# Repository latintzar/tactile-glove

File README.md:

# Artisan Glove

Artisan Glove is a precision glove for recording surface texture, contact and video.

[Website](https://atelierneyra.com/hardware/tactile-glove) · [Documentation](https://docs.atelierneyra.com/tactile-glove/overview/)

The glove lets people collect touch data while they work. The current exploration is a flexible, textured black nitrile glove targeting thousands of taxels across the hand, with recording electronics and a camera at the wrist.

## Dense tactile skin

The compact graphite cuff, hand-facing camera and forest-green pull tab carry through this new typology. Sensing-layer, readout and integration choices are the current investigation. The [dense sensing view](https://atelierneyra.com/hardware/tactile-glove#sensing) visualises 4,096 proposed taxel positions on the same hand photograph. [Current investigation](docs/dense-tactile-skin.md) records the target and engineering questions.

The source below records the earlier twenty-site V4 hardware and Bela experiments.

## Material signatures

In my piezo experiment, I saw distinct spectral signatures for aluminium, wood and sandpaper. Sandpaper had the largest bright feature in the middle of the frequency range; wood a small, thin ridge; aluminium a small-to-medium feature.

*Recreated from my observations.* [Reproduce the figure](docs/material-signatures/README.md).

## Earlier V4 hardware

Twenty sensing locations combine pressure-sensitive film and PVDF vibration sensors. Two IMUs distinguish wrist/camera motion from the hand; an ESP32-S3 records timestamped streams and camera frames to microSD, with USB, Wi-Fi and a browser monitor for inspection. It is a reusable engineering project for people building tactile capture hardware, signal-processing experiments and wearable acquisition systems.

## Source

[Explore CAD](https://atelierneyra.com/hardware/tactile-glove/viewer/) · [Product tour](docs/product-tour.md) · [Native PCB](hardware/glove-v4/electrical/glove-v4-routing-candidate.kicad_pcb) · [Enclosure parts](hardware/glove-v4/enclosure/)

[Setup](docs/setup.md) covers local inspection and the reusable firmware and hardware files.

## What you can explore

| Area | What you can do |
|---|---|
| Cuff design | Inspect the enclosure geometry, camera, battery, connectors, component envelopes and individual parts. |
| Sensing glove | Follow the twenty pressure/PVDF locations, material stack, cut patterns and keyed harness. |
| Electronics | Edit the native KiCad main board and schematics, dorsal IMU tile, footprints, component lists and net mappings. |
| Firmware | Inspect acquisition timing, bus ownership, power transitions, camera deadlines, storage, packet formats and the device browser UI. |
| Verification | Execute the production C++ core and HTTP logic on your computer, decode their actual output, and audit STL clearances. |
| Earlier experiments | Read the Bela sensing pilot and the earlier camera-free V3 board, with their achieved results and open questions kept explicit. |

## Earlier V4 stage

The recorded V4 source is an **engineering beta**. The ESP32-S3 target image was compiled; fresh host checks execute 34 core cases, 13 HTTP cases, 32 protocol/piezo cases and 9 camera-driver cases. The current 561-component V4 board has **20 unconnected items and zero saved physical DRC errors**. Its dorsal IMU tile includes fabrication outputs; the main board awaits routing and manufacturing qualification.

An assembled V4 glove, simultaneous acquisition/camera/radio timing, force calibration, enclosure acceptance and six-hour endurance remain physical validation steps. Rates below describe implementation settings and design targets. [Status and evidence](docs/status.md) distinguish each stage.

The current thin-glove appearance and surgery/sport scenes illustrate the dense tactile-skin investigation. [Design history](docs/design-history.md) records the earlier native V4 geometry and actual validation stage.

| Stream | Implementation setting |
|---|---|
| Pressure | 20 locations × 50 samples/s; electrical levels until per-cell force calibration |
| PVDF vibration | 20 locations × 4,000 samples/s |
| Motion | Two ISM330DHCX IMUs at 833 Hz |
| Camera | OV5640 VGA JPEG, approximately 10 fps target |
| Recording | Timestamped, checksummed tactile/motion streams and JPEG frames on microSD |
| Connections | USB and Wi-Fi full streams; BLE setup, status and selected data |

## Get started

Python 3.11 or later is enough to open the static design viewer:

```sh
git clone https://github.com/latintzar/tactile-glove.git
cd tactile-glove
python3 tools/serve.py
```

Open **http://127.0.0.1:8070/**. The viewer loads the supplied engineering geometry locally. [Setup](docs/setup.md) covers host tests, native KiCad editing, enclosure checks and the pinned ESP-IDF firmware build. Device assembly and programming have their own acceptance guide.

## Source and guides

- [Dense tactile-skin investigation](docs/dense-tactile-skin.md)
- [Product tour and complete journey](docs/product-tour.md)
- [Module map](docs/module-map.md) · [Architecture](docs/architecture.md)
- [Setup](docs/setup.md) · [Verification](docs/verification.md)
- [Current status](docs/status.md) · [Design history and decisions](docs/design-history.md)
- [V4 hardware guide](hardware/glove-v4/README.md) · [Firmware and protocol](firmware/tactile_v4/README.md)
- [Earlier Bela experiment](docs/bela-experiment.md)
- [Contributing and refreshing the inventory](CONTRIBUTING.md)
- [Source inventory and redistribution scope](docs/source-inventory.md) · [Third-party notices](THIRD-PARTY-NOTICES.md)

## Licence and credits

Peter Neyra’s original code, documentation and hardware design are [MIT licensed](LICENSE). Redistributed KiCad library files retain **CC BY-SA 4.0** with KiCad’s design-output exception; Espressif camera sources retain **Apache 2.0**; Seeed and viewer assets retain their own MIT notices. [Third-party notices](THIRD-PARTY-NOTICES.md) identify those boundaries and source revisions.

Made by [Atelier Neyra](https://atelierneyra.com/).

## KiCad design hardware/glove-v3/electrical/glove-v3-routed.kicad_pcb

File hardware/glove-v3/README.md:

# Right-hand tactile glove —V3.3 core

Current completed electrical baseline:20 separately read pressure locations and20 PVDF vibration locations, one button and a diffused RGB indicator. The next complete-product requirement adds continuous finger-facing video for at least six hours, with twelve hours as the stretch target. Its camera, controller and larger-battery power design remain under integration review.

## Files

- `electrical/components.json`:356 fitted components,244 nets,1125 connected endpoints and19 intentional NC pins;40 MPN groups.
- `electrical/glove-v3.kicad_sch`: native schematic; `electrical/glove-v3-routed.kicad_pcb`:90×60×1.6mm four-layer routing. Native reconciliation and KiCad DRC report zero violations, opens or footprint errors.
- `electrical/manufacturing/manifest.json`:18 hashed manufacturing files, Gerbers/drills,356-placement CPL and actual-board assembly drawings. VIPPO epoxy-filled, planarized, copper-capped vias are mandatory at34 SMD-overlap locations.
- `../../firmware/tactile_v3/`: compiled XIAO nRF52840 firmware,130688 bytes flash/21408 bytes static RAM; matching HEX/UF2/debug ELF and source hashes.
- `../../tools/tactile_v3/`: transport, recording and Bluetooth bridge. Wireprotocol2 explicitly records3V reference,1.25V midpoint and2.5V excitation.
- `guide/index.html`, `sensors/assembly.md`, `sensors/wiring.csv`:20 anatomical locations, film orientation, stack construction and six keyed harness branches.
- `enclosure/index.html`: existing500mAh core enclosure. `enclosure/pebble-concept/index.html`: separate rounded CAD concept with actual geometry and constraints; its106×82×34.56mm envelope is not a watch-size product. Camera/largerbattery integration is pending.
- `camera/runtime-and-integration.md`, `camera/runtime-budget.json`, `camera/camera-selection.md`: six-hour power ceiling, exact battery candidate, optics and heat checks, with sources.
- `procurement/jlc-v33/`: current quote files and exact-part availability/substitution records. The earlier V3.1/V3.2 quote artifacts are historical partial quotes.

## Verified in software and simulation

- `verification/final-software-v33.json`:488 distinct repository tests plus four subtests pass; JavaScript syntax passes.
- `verification/firmware-simulation.md`:41 actual-sketch scenarios pass ASan/UBSan, including acquisition, timing rollover, button, power qualification, malformed commands, transport faults, backpressure and IMU failures.
- `verification/signal-chain/piezo-end-to-end.md`:520 modeled ADC samples survive USB and BLE selected-channel transport exactly, with timestamps and six RMS/peak windows independently checked.
- `verification/power-simulation.md`: corrected reference, excitation buffer, shutdown/protection and component-current checks.
- `verification/analog-signal-chain.md`:16/18 primary Microchip/Nexperia transient cases complete; two late-recovery solver failures also complete with explicitly bounded1fF numerical stabilization. Seven TI mux/driver cases complete, informing6µs dynamic and12µs pressure waits.

These checks do not substitute for physical timing, radio, current, thermal or tactile characterization.

## Use of the tactile core

Hold the button0.8s from sleep and release to wake; continue to3s for a120s pairing window. While running, tap to pause/resume or hold1.5s to sleep after release. Blue indicates startup/pairing; green indicates ready/collecting; amber indicates low or unqualified battery; a red double flash indicates ADC trouble.

Target acquisition is20 vibration channels at4kS/s each and20 pressure channels at50S/s each. USB carries full raw data. BLE carries all-channel features or one selected raw channel plus IMU/health. Invalid-power and dropped-frame flags remain in recordings. The current battery configuration is a protected500mAh cell with100mA charging; it is not the six-hour camera system.

## Manufacturing and capability scope

The tactile board is a routed engineering prototype. Its specified VIPPO process, complete sourcing, assembly quote and first-article acceptance remain required. The camera integration changes the MCU/power/firmware design and enclosure; it is not yet a factory release. The initialUS$150–200 complete delivered target remains unverified. No purchase or email has been sent.

Pressure readings require cell calibration; vibration plots are signal measurements, not measured surface Ra. The hardware does not directly measure every finger joint or drift-free hidden-hand position. Rendering and demos must preserve those distinctions.

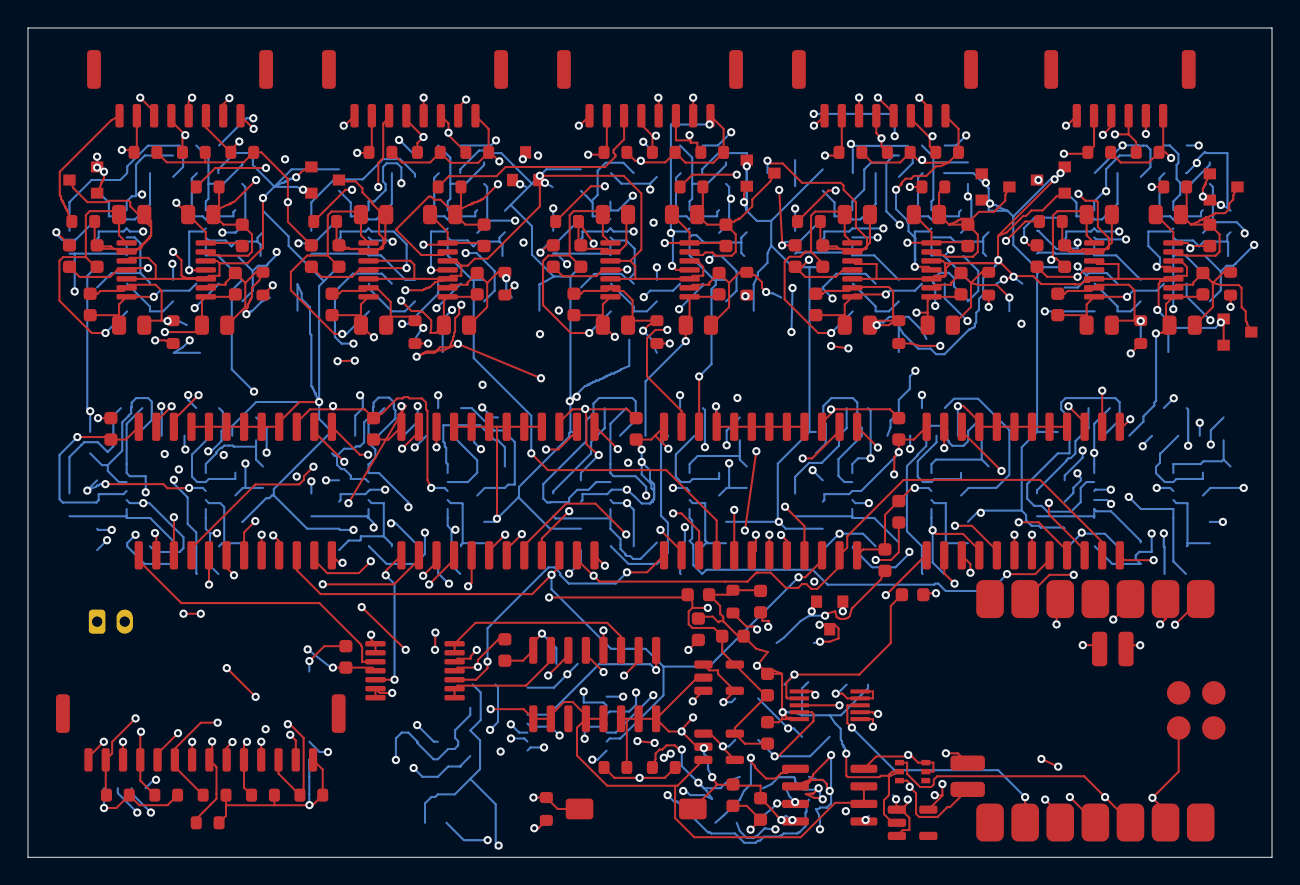
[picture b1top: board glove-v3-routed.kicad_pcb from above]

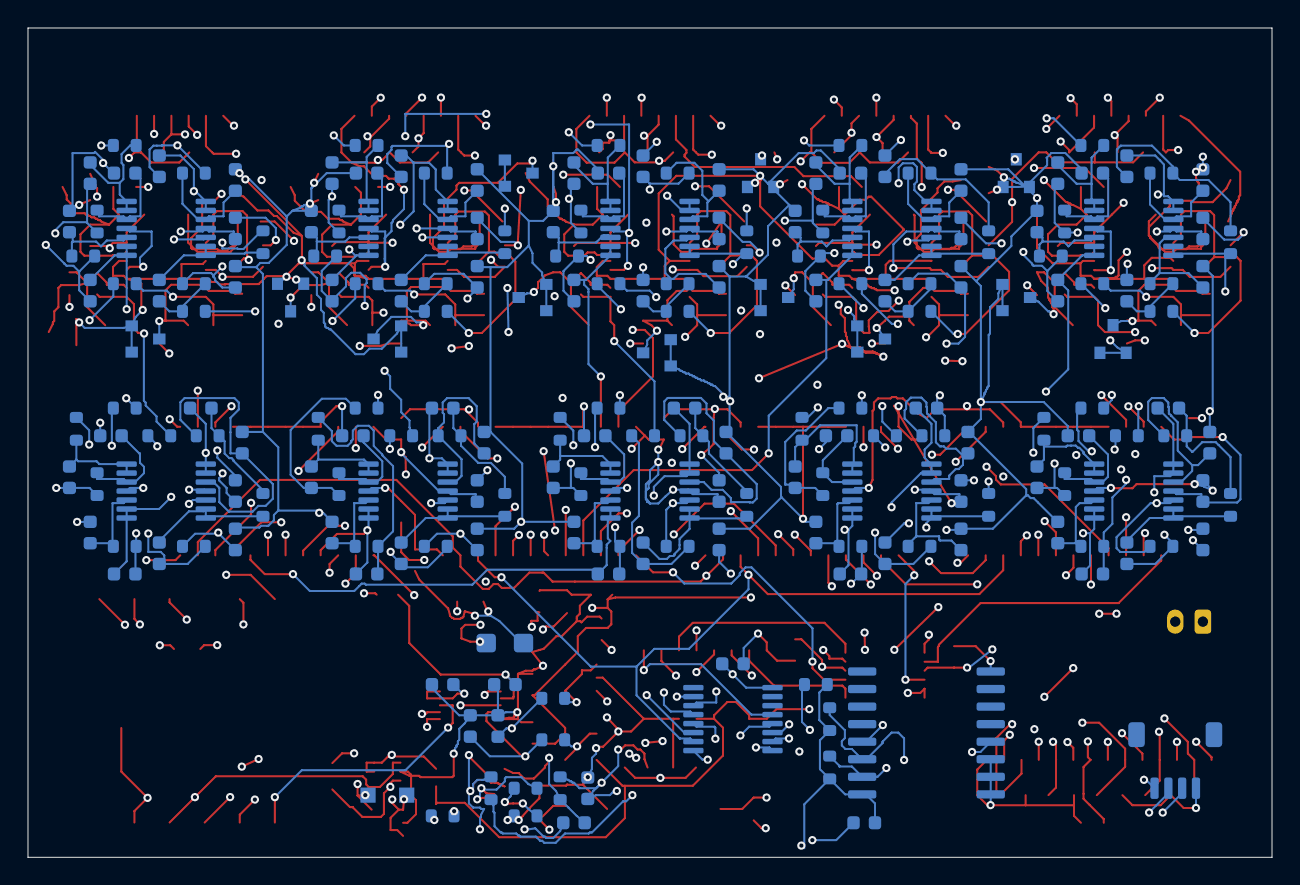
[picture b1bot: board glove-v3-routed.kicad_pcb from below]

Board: 4 copper layers, 90.0 x 60.0 mm, 356 parts (215 on the bottom side), 243 nets.

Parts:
C1, C6, C11, C16, C21, C26, C31, C36, C41, C46, C51, C56, C61, C66, C71, C76, C81, C86, C91, C96: GRM1885C1H471JA01D; C_0603_1608Metric
C2, C7, C12, C17, C22, C27, C32, C37, C42, C47, C52, C57, C62, C67, C72, C77, C82, C87, C92, C97: C0603C123J3GACAUTO; C_0603_1608Metric
C3, C8, C13, C18, C23, C28, C33, C38, C43, C48, C53, C58, C63, C68, C73, C78, C83, C88, C93, C98: GRM1885C1H103JA01D; C_0603_1608Metric
C4, C9, C14, C19, C24, C29, C34, C39, C44, C49, C54, C59, C64, C69, C74, C79, C84, C89, C94, C99: C0603C153J3GACAUTO; C_0603_1608Metric
C5, C10, C15, C20, C25, C30, C35, C40, C45, C50, C55, C60, C65, C70, C75, C80, C85, C90, C95, C100: GRM1885C1H222JA01D; C_0603_1608Metric
C101, C102, C103, C104, C108, C133, C135, C136, C141: GRM188R61A105KA61D; C_0603_1608Metric
C105, C107, C109, C110, C111, C112, C113, C114, C115, C116, C117, C118, C119, C120, C121, C122, C123, C124, C125, C126, C127, C128, C129, C130, C131, C132, C137, C140: GRM188R71H104KA93D; C_0603_1608Metric
C106: TAJA685K010RNJ; CP_EIA-3216-18_Kemet-A
C134, C138: GRM1885C1H102JA01D; C_0603_1608Metric
C139: GRM188R71C104KA01D; C_0603_1608Metric
D1: PMEG2010ER,115; D_SOD-123F
D2, D3, D4, D5, D6, D7, D8, D9, D10, D11, D12, D13, D14, D15, D16, D17, D18, D19, D20, D21: BAV199,215; SOT-23
J1: 102010469; XIAO-nRF52840-SMD-kicad7
J2: B2B-PH-K-S(LF)(SN); JST_PH_B2B-PH-K_1x02_P2.00mm_Vertical
J3: SM04B-SRSS-TB(LF)(SN); JST_SH_SM04B-SRSS-TB_1x04-1MP_P1.00mm_Horizontal
J5: BM06B-GHS-TBT(LF)(SN); JST_GH_BM06B-GHS-TBT_1x06-1MP_P1.25mm_Vertical
J6, J7, J8, J9: BM08B-GHS-TBT(LF)(SN); JST_GH_BM08B-GHS-TBT_1x08-1MP_P1.25mm_Vertical
J10: BM14B-GHS-TBT(LF)(SN); JST_GH_BM14B-GHS-TBT_1x14-1MP_P1.25mm_Vertical
R1, R8, R15, R22, R29, R36, R43, R50, R57, R64, R71, R78, R85, R92, R99, R106, R113, R120, R127, R134: RV0805FR-0722ML; R_0805_2012Metric
R2, R9, R16, R23, R30, R37, R44, R51, R58, R65, R72, R79, R86, R93, R100, R107, R114, R121, R128, R135, R146: RC0603FR-07100KL; R_0603_1608Metric
R3, R4, R10, R11, R17, R18, R24, R25, R31, R32, R38, R39, R45, R46, R52, R53, R59, R60, R66, R67, R73, R74, R80, R81, R87, R88, R94, R95, R101, R102, R108, R109, R115, R116, R122, R123, R129, R130, R136, R137: RC0603FR-0714K7L; R_0603_1608Metric
R5, R6, R12, R13, R19, R20, R26, R27, R33, R34, R40, R41, R47, R48, R54, R55, R61, R62, R68, R69, R75, R76, R82, R83, R89, R90, R96, R97, R103, R104, R110, R111, R117, R118, R124, R125, R131, R132, R138, R139: RC0603FR-0727K4L; R_0603_1608Metric
R7, R14, R21, R28, R35, R42, R49, R56, R63, R70, R77, R84, R91, R98, R105, R112, R119, R126, R133, R140, R141, R142, R147, R149, R151, R154: RC0603FR-0710KL; R_0603_1608Metric
R143, R148: RC0603FR-0722RL; R_0603_1608Metric
R144, R145, R152: RC0603FR-074K7L; R_0603_1608Metric
R150: RC0603FR-072KL; R_0603_1608Metric
R153: RC0603FR-0747RL; R_0603_1608Metric
SW1: PTS636SK43SMTR-LFS; SW_PTS636_SK43_G
U1: TLV75518PDBVR; SOT-23-5
U2: REF3330AIDBZR; SOT-23
U3: MCP6002T-I/SN; SOIC-8_3.9x4.9mm_P1.27mm
U4: MCP33131D-10-I/MS; MSOP-10_3x3mm_P0.5mm
U5, U29: OPA320AIDBVR; SOT-23-5
U6, U7, U8, U9: CD74HC4067M; SOIC-24W_7.5x15.4mm_P1.27mm
U10: CD74HC4052M; SOIC-16_3.9x9.9mm_P1.27mm
U11, U12, U13, U14, U15, U16, U17, U18, U19, U20, U21, U22, U23, U24, U25: MCP6004T-I/ST; TSSOP-14_4.4x5mm_P0.65mm
U26: OPA4323IPWR; TSSOP-14_4.4x5mm_P0.65mm
U27: TCA9534DWR; SOIC-16W_7.5x10.3mm_P1.27mm
U28: TPS22919DCKT; SOT-363_SC-70-6
U30: SN74AHC595PWR; TSSOP-16_4.4x5mm_P0.65mm

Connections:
1V8: C102.1, C104.1, D1.2, U1.5, U4.2
3V3: C132.1, C135.1, J1.12, J3.2, R144.1, R145.1, R147.1, R149.1, U27.16, U28.1
3V3A: C101.1, C105.1, C107.1, C108.1, C109.1, C110.1, C111.1, C112.1, C113.1, C114.1, C115.1, C116.1, C117.1, C118.1, C119.1, C120.1, C121.1, C122.1, C123.1, C124.1, C125.1, C126.1, C127.1, C128.1, C129.1, C130.1, C131.1, C136.1, C137.1, C139.1, D1.1, U1.1, U1.3, U2.1, U3.8, U4.9, U4.10, U5.5, U6.24, U7.24, U8.24, U9.24, U10.16, U11.4, U12.4, U13.4, U14.4, U15.4, U16.4, U17.4, U18.4, U19.4, U20.4, U21.4, U22.4, U23.4, U24.4, U25.4, U26.4, U28.5, U28.6, U29.5, U30.10, U30.16
ADC_AIN+: C134.1, R143.2, U4.3
ADC_AIN-: C138.1, R148.2, U4.4
ADC_CNV: J1.11, U4.6
ADC_DRIVER_OUT: R143.1, U5.1, U5.4
ADC_MISO: J1.10, U4.7
ADC_MUX: U5.3, U10.13
ADC_NEG_OUT: R148.1, U29.1, U29.4
ADC_SCK: J1.9, U4.8
ANALOG_EN: J1.22, R146.1, U28.3
BAT+: J1.19, J2.1
BTN0: R149.2, SW1.1, U27.4
CHG_IN_H1: C91.2, D20.3, R127.2, R128.2, U15.9
CHG_IN_H2: C96.2, D21.3, R134.2, R135.2, U15.13
CHG_IN_I1: C1.2, D2.3, R1.2, R2.2, U11.2
CHG_IN_I2: C6.2, D3.3, R8.2, R9.2, U11.6
CHG_IN_I3: C11.2, D4.3, R15.2, R16.2, U11.9
CHG_IN_L1: C46.2, D11.3, R64.2, R65.2, U13.6
CHG_IN_L2: C51.2, D12.3, R71.2, R72.2, U13.9
CHG_IN_L3: C56.2, D13.3, R78.2, R79.2, U13.13
CHG_IN_M1: C16.2, D5.3, R22.2, R23.2, U11.13
CHG_IN_M2: C21.2, D6.3, R29.2, R30.2, U12.2
CHG_IN_M3: C26.2, D7.3, R36.2, R37.2, U12.6
CHG_IN_P1: C71.2, D16.3, R99.2, R100.2, U14.9
CHG_IN_P2: C76.2, D17.3, R106.2, R107.2, U14.13
CHG_IN_P3: C81.2, D18.3, R113.2, R114.2, U15.2
CHG_IN_P4: C86.2, D19.3, R120.2, R121.2, U15.6
CHG_IN_R1: C31.2, D8.3, R43.2, R44.2, U12.9
CHG_IN_R2: C36.2, D9.3, R50.2, R51.2, U12.13
CHG_IN_R3: C41.2, D10.3, R57.2, R58.2, U13.2
CHG_IN_T1: C61.2, D14.3, R85.2, R86.2, U14.2
CHG_IN_T2: C66.2, D15.3, R92.2, R93.2, U14.6
CHG_OUT_H1: C91.1, R127.1, R129.1, U15.8
CHG_OUT_H2: C96.1, R134.1, R136.1, U15.14
CHG_OUT_I1: C1.1, R1.1, R3.1, U11.1
CHG_OUT_I2: C6.1, R8.1, R10.1, U11.7
CHG_OUT_I3: C11.1, R15.1, R17.1, U11.8
CHG_OUT_L1: C46.1, R64.1, R66.1, U13.7
CHG_OUT_L2: C51.1, R71.1, R73.1, U13.8
CHG_OUT_L3: C56.1, R78.1, R80.1, U13.14
CHG_OUT_M1: C16.1, R22.1, R24.1, U11.14
CHG_OUT_M2: C21.1, R29.1, R31.1, U12.1
CHG_OUT_M3: C26.1, R36.1, R38.1, U12.7
CHG_OUT_P1: C71.1, R99.1, R101.1, U14.8
CHG_OUT_P2: C76.1, R106.1, R108.1, U14.14
CHG_OUT_P3: C81.1, R113.1, R115.1, U15.1
CHG_OUT_P4: C86.1, R120.1, R122.1, U15.7
CHG_OUT_R1: C31.1, R43.1, R45.1, U12.8
CHG_OUT_R2: C36.1, R50.1, R52.1, U12.14
CHG_OUT_R3: C41.1, R57.1, R59.1, U13.1
CHG_OUT_T1: C61.1, R85.1, R87.1, U14.1
CHG_OUT_T2: C66.1, R92.1, R94.1, U14.7
GND: C101.2, C102.2, C103.2, C104.2, C105.2, C106.2, C107.2, C108.2, C109.2, C110.2, C111.2, C112.2, C113.2, C114.2, C115.2, C116.2, C117.2, C118.2, C119.2, C120.2, C121.2, C122.2, C123.2, C124.2, C125.2, C126.2, C127.2, C128.2, C129.2, C130.2, C131.2, C132.2, C133.2, C134.2, C135.2, C136.2, C137.2, C138.2, C139.2, C141.2, J1.13, J1.18, J1.20, J2.2, J3.1, J5.6, J6.8, J7.8, J8.8, J9.8, J10.14, R7.2, R14.2, R21.2, R28.2, R35.2, R42.2, R49.2, R56.2, R63.2, R70.2, R77.2, R84.2, R91.2, R98.2, R105.2, R112.2, R119.2, R126.2, R133.2, R140.2, R142.2, R146.2, R151.2, SW1.2, U1.2, U2.3, U3.4, U4.5, U5.2, U6.12, U6.15, U7.12, U7.15, U8.12, U8.15, U9.12, U9.15, U10.6, U10.7, U10.8, U11.11, U12.11, U13.11, U14.11, U15.11, U16.11, U17.11, U18.11, U19.11, U20.11, U21.11, U22.11, U23.11, U24.11, U25.11, U26.11, U27.1, U27.2, U27.3, U27.8, U28.2, U29.2, U30.8, U30.13
I2C_SCL: J1.6, J3.4, R145.2, U27.14
I2C_SDA: J1.5, J3.3, R144.2, U27.15
MUX1_BUF: U10.12, U26.1, U26.2
MUX1_COM: U6.1, U26.3
MUX2_BUF: U10.14, U26.6, U26.7
MUX2_COM: U7.1, U26.5
MUX3_BUF: U10.15, U26.8, U26.9
MUX3_COM: U8.1, U26.10
MUX4_BUF: U10.11, U26.13, U26.14
MUX4_COM: U9.1, U26.12
MUX_A0: U6.10, U7.10, U8.10, U9.10, U30.15
MUX_A1: U6.11, U7.11, U8.11, U9.11, U30.1
MUX_A2: U6.14, U7.14, U8.14, U9.14, U30.2
MUX_A3: U6.13, U7.13, U8.13, U9.13, U30.3
MUX_BANK0: U10.10, U30.4
MUX_BANK1: U10.9, U30.5
MUX_RCLK: J1.3, U30.12
MUX_SER: J1.2, U30.14
MUX_SRCLK: J1.1, U30.11
PRESS_H1: J10.10, R133.1, U7.23
PRESS_H2: J10.12, R140.1, U7.22
PRESS_I1: J6.2, R7.1, U6.9
PRESS_I2: J6.4, R14.1, U6.8
PRESS_I3: J6.6, R21.1, U6.7
PRESS_L1: J9.2, R70.1, U6.22
PRESS_L2: J9.4, R77.1, U7.9
PRESS_L3: J9.6, R84.1, U7.8
PRESS_M1: J7.2, R28.1, U6.6
PRESS_M2: J7.4, R35.1, U6.5
PRESS_M3: J7.6, R42.1, U6.4
PRESS_P1: J10.2, R105.1, U7.5
PRESS_P2: J10.4, R112.1, U7.4
PRESS_P3: J10.6, R119.1, U7.3
PRESS_P4: J10.8, R126.1, U7.2
PRESS_R1: J8.2, R49.1, U6.3
PRESS_R2: J8.4, R56.1, U6.2
PRESS_R3: J8.6, R63.1, U6.23
PRESS_T1: J5.2, R91.1, U7.7
PRESS_T2: J5.4, R98.1, U7.6
PVDF_H1: J10.9, R128.1
PVDF_H2: J10.11, R135.1
PVDF_I1: J6.1, R2.1
PVDF_I2: J6.3, R9.1
PVDF_I3: J6.5, R16.1
PVDF_L1: J9.1, R65.1
PVDF_L2: J9.3, R72.1
PVDF_L3: J9.5, R79.1
PVDF_M1: J7.1, R23.1
PVDF_M2: J7.3, R30.1
PVDF_M3: J7.5, R37.1
PVDF_P1: J10.1, R100.1
PVDF_P2: J10.3, R107.1
PVDF_P3: J10.5, R114.1
PVDF_P4: J10.7, R121.1
PVDF_R1: J8.1, R44.1
PVDF_R2: J8.3, R51.1
PVDF_R3: J8.5, R58.1
PVDF_T1: J5.1, R86.1
PVDF_T2: J5.3, R93.1
S1_A_H1: C92.1, R129.2, R130.1
S1_A_H2: C97.1, R136.2, R137.1
S1_A_I1: C2.1, R3.2, R4.1
S1_A_I2: C7.1, R10.2, R11.1
S1_A_I3: C12.1, R17.2, R18.1
S1_A_L1: C47.1, R66.2, R67.1
S1_A_L2: C52.1, R73.2, R74.1
S1_A_L3: C57.1, R80.2, R81.1
S1_A_M1: C17.1, R24.2, R25.1
S1_A_M2: C22.1, R31.2, R32.1
S1_A_M3: C27.1, R38.2, R39.1
S1_A_P1: C72.1, R101.2, R102.1
S1_A_P2: C77.1, R108.2, R109.1
S1_A_P3: C82.1, R115.2, R116.1
S1_A_P4: C87.1, R122.2, R123.1
S1_A_R1: C32.1, R45.2, R46.1
S1_A_R2: C37.1, R52.2, R53.1
S1_A_R3: C42.1, R59.2, R60.1
S1_A_T1: C62.1, R87.2, R88.1
S1_A_T2: C67.1, R94.2, R95.1
S1_B_H1: C93.1, R130.2, U25.3
S1_B_H2: C98.1, R137.2, U25.10
S1_B_I1: C3.1, R4.2, U16.3
S1_B_I2: C8.1, R11.2, U16.10
S1_B_I3: C13.1, R18.2, U17.3
S1_B_L1: C48.1, R67.2, U20.10
S1_B_L2: C53.1, R74.2, U21.3
S1_B_L3: C58.1, R81.2, U21.10
S1_B_M1: C18.1, R25.2, U17.10
S1_B_M2: C23.1, R32.2, U18.3
S1_B_M3: C28.1, R39.2, U18.10
S1_B_P1: C73.1, R102.2, U23.3
S1_B_P2: C78.1, R109.2, U23.10
S1_B_P3: C83.1, R116.2, U24.3
S1_B_P4: C88.1, R123.2, U24.10
S1_B_R1: C33.1, R46.2, U19.3
S1_B_R2: C38.1, R53.2, U19.10
S1_B_R3: C43.1, R60.2, U20.3
S1_B_T1: C63.1, R88.2, U22.3
S1_B_T2: C68.1, R95.2, U22.10
S1_OUT_H1: C92.2, R131.1, U25.1, U25.2
S1_OUT_H2: C97.2, R138.1, U25.8, U25.9
S1_OUT_I1: C2.2, R5.1, U16.1, U16.2
S1_OUT_I2: C7.2, R12.1, U16.8, U16.9
S1_OUT_I3: C12.2, R19.1, U17.1, U17.2
S1_OUT_L1: C47.2, R68.1, U20.8, U20.9
S1_OUT_L2: C52.2, R75.1, U21.1, U21.2
S1_OUT_L3: C57.2, R82.1, U21.8, U21.9
S1_OUT_M1: C17.2, R26.1, U17.8, U17.9
S1_OUT_M2: C22.2, R33.1, U18.1, U18.2
S1_OUT_M3: C27.2, R40.1, U18.8, U18.9
S1_OUT_P1: C72.2, R103.1, U23.1, U23.2
S1_OUT_P2: C77.2, R110.1, U23.8, U23.9
S1_OUT_P3: C82.2, R117.1, U24.1, U24.2
S1_OUT_P4: C87.2, R124.1, U24.8, U24.9
S1_OUT_R1: C32.2, R47.1, U19.1, U19.2
S1_OUT_R2: C37.2, R54.1, U19.8, U19.9
S1_OUT_R3: C42.2, R61.1, U20.1, U20.2
S1_OUT_T1: C62.2, R89.1, U22.1, U22.2
S1_OUT_T2: C67.2, R96.1, U22.8, U22.9
S2_A_H1: C94.1, R131.2, R132.1
S2_A_H2: C99.1, R138.2, R139.1
S2_A_I1: C4.1, R5.2, R6.1
S2_A_I2: C9.1, R12.2, R13.1
S2_A_I3: C14.1, R19.2, R20.1
S2_A_L1: C49.1, R68.2, R69.1
S2_A_L2: C54.1, R75.2, R76.1
S2_A_L3: C59.1, R82.2, R83.1
S2_A_M1: C19.1, R26.2, R27.1
S2_A_M2: C24.1, R33.2, R34.1
S2_A_M3: C29.1, R40.2, R41.1
S2_A_P1: C74.1, R103.2, R104.1
S2_A_P2: C79.1, R110.2, R111.1
S2_A_P3: C84.1, R117.2, R118.1
S2_A_P4: C89.1, R124.2, R125.1
S2_A_R1: C34.1, R47.2, R48.1
S2_A_R2: C39.1, R54.2, R55.1
S2_A_R3: C44.1, R61.2, R62.1
S2_A_T1: C64.1, R89.2, R90.1
S2_A_T2: C69.1, R96.2, R97.1
S2_B_H1: C95.1, R132.2, U25.5
S2_B_H2: C100.1, R139.2, U25.12
S2_B_I1: C5.1, R6.2, U16.5
S2_B_I2: C10.1, R13.2, U16.12
S2_B_I3: C15.1, R20.2, U17.5
S2_B_L1: C50.1, R69.2, U20.12
S2_B_L2: C55.1, R76.2, U21.5
S2_B_L3: C60.1, R83.2, U21.12
S2_B_M1: C20.1, R27.2, U17.12
S2_B_M2: C25.1, R34.2, U18.5
S2_B_M3: C30.1, R41.2, U18.12
S2_B_P1: C75.1, R104.2, U23.5
S2_B_P2: C80.1, R111.2, U23.12
S2_B_P3: C85.1, R118.2, U24.5
S2_B_P4: C90.1, R125.2, U24.12
S2_B_R1: C35.1, R48.2, U19.5
S2_B_R2: C40.1, R55.2, U19.12
S2_B_R3: C45.1, R62.2, U20.5
S2_B_T1: C65.1, R90.2, U22.5
S2_B_T2: C70.1, R97.2, U22.12
S2_OUT_H1: C94.2, U9.23, U25.6, U25.7
S2_OUT_H2: C99.2, U9.22, U25.13, U25.14
S2_OUT_I1: C4.2, U8.9, U16.6, U16.7
S2_OUT_I2: C9.2, U8.8, U16.13, U16.14
S2_OUT_I3: C14.2, U8.7, U17.6, U17.7
S2_OUT_L1: C49.2, U8.22, U20.13, U20.14
S2_OUT_L2: C54.2, U9.9, U21.6, U21.7
S2_OUT_L3: C59.2, U9.8, U21.13, U21.14
S2_OUT_M1: C19.2, U8.6, U17.13, U17.14
S2_OUT_M2: C24.2, U8.5, U18.6, U18.7
S2_OUT_M3: C29.2, U8.4, U18.13, U18.14
S2_OUT_P1: C74.2, U9.5, U23.6, U23.7
S2_OUT_P2: C79.2, U9.4, U23.13, U23.14
S2_OUT_P3: C84.2, U9.3, U24.6, U24.7
S2_OUT_P4: C89.2, U9.2, U24.13, U24.14
S2_OUT_R1: C34.2, U8.3, U19.6, U19.7
S2_OUT_R2: C39.2, U8.2, U19.13, U19.14
S2_OUT_R3: C44.2, U8.23, U20.6, U20.7
S2_OUT_T1: C64.2, U9.7, U22.6, U22.7
S2_OUT_T2: C69.2, U9.6, U22.13, U22.14
VEXC2V5: C141.1, J5.5, J6.7, J7.7, J8.7, J9.7, J10.13, R141.1, R153.2, R154.1
VEXC_DIV: R150.2, R151.1, U3.3
VEXC_DRV: C140.1, R153.1, U3.1
VEXC_FB: C140.2, R154.2, U3.2
VMID1V25: C3.2, C5.2, C8.2, C10.2, C13.2, C15.2, C18.2, C20.2, C23.2, C25.2, C28.2, C30.2, C33.2, C35.2, C38.2, C40.2, C43.2, C45.2, C48.2, C50.2, C53.2, C55.2, C58.2, C60.2, C63.2, C65.2, C68.2, C70.2, C73.2, C75.2, C78.2, C80.2, C83.2, C85.2, C88.2, C90.2, C93.2, C95.2, C98.2, C100.2, D2.1, D2.2, D3.1, D3.2, D4.1, D4.2, D5.1, D5.2, D6.1, D6.2, D7.1, D7.2, D8.1, D8.2, D9.1, D9.2, D10.1, D10.2, D11.1, D11.2, D12.1, D12.2, D13.1, D13.2, D14.1, D14.2, D15.1, D15.2, D16.1, D16.2, D17.1, D17.2, D18.1, D18.2, D19.1, D19.2, D20.1, D20.2, D21.1, D21.2, U3.6, U3.7, U6.16, U6.17, U6.18, U6.19, U6.20, U6.21, U7.16, U7.17, U7.18, U7.19, U7.20, U7.21, U8.16, U8.17, U8.18, U8.19, U8.20, U8.21, U9.16, U9.17, U9.18, U9.19, U9.20, U9.21, U10.1, U10.2, U10.4, U10.5, U11.3, U11.5, U11.10, U11.12, U12.3, U12.5, U12.10, U12.12, U13.3, U13.5, U13.10, U13.12, U14.3, U14.5, U14.10, U14.12, U15.3, U15.5, U15.10, U15.12, U29.3
VMID_BUF_IN: R152.2, U3.5
VMID_DIV: C133.1, R141.2, R142.1, R152.1
VREF3V0: C103.1, C106.1, R150.1, U2.2, U4.1
WAKE_IRQ: J1.21, R147.2, U27.13

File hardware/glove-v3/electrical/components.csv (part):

Designator,Role,MPN,Package,Value,Status
J1,J_XIAO,102010469,module 21x17.8mm,,topology corrected; physical CAD and supplier verification pending
J2,J_BAT,B2B-PH-K-S(LF)(SN),JST PH 2,,topology corrected; physical CAD and supplier verification pending
U1,U_LDO,TLV75518PDBVR,SOT-23-5,,topology corrected; physical CAD and supplier verification pending
U2,U_REF,REF3330AIDBZR,SOT-23-3,,topology corrected; physical CAD and supplier verification pending
U3,U_VMID,MCP6002T-I/SN,SOIC-8,,topology corrected; physical CAD and supplier verification pending
U4,U_ADC,MCP33131D-10-I/MS,MSOP-10,,topology corrected; physical CAD and supplier verification pending
U5,U_ADC_DRV,OPA320AIDBVR,SOT-23-5,,topology corrected; physical CAD and supplier verification pending
U6,U_MUX1,CD74HC4067M,SOIC-24,,topology corrected; physical CAD and supplier verification pending
U7,U_MUX2,CD74HC4067M,SOIC-24,,topology corrected; physical CAD and supplier verification pending
U8,U_MUX3,CD74HC4067M,SOIC-24,,topology corrected; physical CAD and supplier verification pending
U9,U_MUX4,CD74HC4067M,SOIC-24,,topology corrected; physical CAD and supplier verification pending
U10,U_MUX_FINAL,CD74HC4052M,SOIC-16,,topology corrected; physical CAD and supplier verification pending
U11,U_CHG1,MCP6004T-I/ST,TSSOP-14,,topology corrected; physical CAD and supplier verification pending
U12,U_CHG2,MCP6004T-I/ST,TSSOP-14,,topology corrected; physical CAD and supplier verification pending
U13,U_CHG3,MCP6004T-I/ST,TSSOP-14,,topology corrected; physical CAD and supplier verification pending
U14,U_CHG4,MCP6004T-I/ST,TSSOP-14,,topology corrected; physical CAD and supplier verification pending
U15,U_CHG5,MCP6004T-I/ST,TSSOP-14,,topology corrected; physical CAD and supplier verification pending
U16,U_FILT1,MCP6004T-I/ST,TSSOP-14,,topology corrected; physical CAD and supplier verification pending
U17,U_FILT2,MCP6004T-I/ST,TSSOP-14,,topology corrected; physical CAD and supplier verification pending
U18,U_FILT3,MCP6004T-I/ST,TSSOP-14,,topology corrected; physical CAD and supplier verification pending
U19,U_FILT4,MCP6004T-I/ST,TSSOP-14,,topology corrected; physical CAD and supplier verification pending
U20,U_FILT5,MCP6004T-I/ST,TSSOP-14,,topology corrected; physical CAD and supplier verification pending
U21,U_FILT6,MCP6004T-I/ST,TSSOP-14,,topology corrected; physical CAD and supplier verification pending
U22,U_FILT7,MCP6004T-I/ST,TSSOP-14,,topology corrected; physical CAD and supplier verification pending
U23,U_FILT8,MCP6004T-I/ST,TSSOP-14,,topology corrected; physical CAD and supplier verification pending
U24,U_FILT9,MCP6004T-I/ST,TSSOP-14,,topology corrected; physical CAD and supplier verification pending
U25,U_FILT10,MCP6004T-I/ST,TSSOP-14,,topology corrected; physical CAD and supplier verification pending
U26,U_BANK1,OPA4323IPWR,TSSOP-14,,topology corrected; physical CAD and supplier verification pending
J3,J_IMU,SM04B-SRSS-TB(LF)(SN),JST SH 1mm side entry 4,,topology corrected; physical CAD and supplier verification pending
U27,U_IOX,TCA9534DWR,SOIC-16,,topology corrected; physical CAD and supplier verification pending
J5,J_THUMB,BM06B-GHS-TBT(LF)(SN),JST GH 1.25mm top-entry,,topology corrected; physical CAD and supplier verification pending
J6,J_INDEX,BM08B-GHS-TBT(LF)(SN),JST GH 1.25mm top-entry,,topology corrected; physical CAD and supplier verification pending
J7,J_MIDDLE,BM08B-GHS-TBT(LF)(SN),JST GH 1.25mm top-entry,,topology corrected; physical CAD and supplier verification pending
J8,J_RING,BM08B-GHS-TBT(LF)(SN),JST GH 1.25mm top-entry,,topology corrected; physical CAD and supplier verification pending
J9,J_LITTLE,BM08B-GHS-TBT(LF)(SN),JST GH 1.25mm top-entry,,topology corrected; physical CAD and supplier verification pending
J10,J_PALM_HEEL,BM14B-GHS-TBT(LF)(SN),JST GH 1.25mm top-entry,,topology corrected; physical CAD and supplier verification pending
R1,RFB_I1,RV0805FR-0722ML,0805,22Meg,10% exact order candidate; manufacturer evidence audit in progress
C1,CFB_I1,GRM1885C1H471JA01D,0603,470p,topology corrected; physical CAD and supplier verification pending
R2,RIN_I1,RC0603FR-07100KL,0603,100k,topology corrected; physical CAD and supplier verification pending
R3,RS1A_I1,RC0603FR-0714K7L,0603,14.7k,topology corrected; physical CAD and supplier verification pending
R4,RS1B_I1,RC0603FR-0714K7L,0603,14.7k,topology corrected; physical CAD and supplier verification pending
C2,CS1FB_I1,C0603C123J3GACAUTO,0603,12n,candidate exact order awaiting independent source confirmation
C3,CS1G_I1,GRM1885C1H103JA01D,0603,10n,topology corrected; physical CAD and supplier verification pending
R5,RS2A_I1,RC0603FR-0727K4L,0603,27.4k,topology corrected; physical CAD and supplier verification pending
R6,RS2B_I1,RC0603FR-0727K4L,0603,27.4k,topology corrected; physical CAD and supplier verification pending
C4,CS2FB_I1,C0603C153J3GACAUTO,0603,15n,order confirmed; manufacturer drawing crosscheck pending
C5,CS2G_I1,GRM1885C1H222JA01D,0603,2.2n,topology corrected; physical CAD and supplier verification pending
R7,RPD_I1,RC0603FR-0710KL,0603,10k,topology corrected; physical CAD and supplier verification pending
R8,RFB_I2,RV0805FR-0722ML,0805,22Meg,10% exact order candidate; manufacturer evidence audit in progress
C6,CFB_I2,GRM1885C1H471JA01D,0603,470p,topology corrected; physical CAD and supplier verification pending
R9,RIN_I2,RC0603FR-07100KL,0603,100k,topology corrected; physical CAD and supplier verification pending
R10,RS1A_I2,RC0603FR-0714K7L,0603,14.7k,topology corrected; physical CAD and supplier verification pending
R11,RS1B_I2,RC0603FR-0714K7L,0603,14.7k,topology corrected; physical CAD and supplier verification pending
C7,CS1FB_I2,C0603C123J3GACAUTO,0603,12n,candidate exact order awaiting independent source confirmation
C8,CS1G_I2,GRM1885C1H103JA01D,0603,10n,topology corrected; physical CAD and supplier verification pending
R12,RS2A_I2,RC0603FR-0727K4L,0603,27.4k,topology corrected; physical CAD and supplier verification pending
R13,RS2B_I2,RC0603FR-0727K4L,0603,27.4k,topology corrected; physical CAD and supplier verification pending
C9,CS2FB_I2,C0603C153J3GACAUTO,0603,15n,order confirmed; manufacturer drawing crosscheck pending
C10,CS2G_I2,GRM1885C1H222JA01D,0603,2.2n,topology corrected; physical CAD and supplier verification pending
R14,RPD_I2,RC0603FR-0710KL,0603,10k,topology corrected; physical CAD and supplier verification pending
R15,RFB_I3,RV0805FR-0722ML,0805,22Meg,10% exact order candidate; manufacturer evidence audit in progress
C11,CFB_I3,GRM1885C1H471JA01D,0603,470p,topology corrected; physical CAD and supplier verification pending
R16,RIN_I3,RC0603FR-07100KL,0603,100k,topology corrected; physical CAD and supplier verification pending
R17,RS1A_I3,RC0603FR-0714K7L,0603,14.7k,topology corrected; physical CAD and supplier verification pending
R18,RS1B_I3,RC0603FR-0714K7L,0603,14.7k,topology corrected; physical CAD and supplier verification pending
C12,CS1FB_I3,C0603C123J3GACAUTO,0603,12n,candidate exact order awaiting independent source confirmation
C13,CS1G_I3,GRM1885C1H103JA01D,0603,10n,topology corrected; physical CAD and supplier verification pending
R19,RS2A_I3,RC0603FR-0727K4L,0603,27.4k,topology corrected; physical CAD and supplier verification pending
R20,RS2B_I3,RC0603FR-0727K4L,0603,27.4k,topology corrected; physical CAD and supplier verification pending
C14,CS2FB_I3,C0603C153J3GACAUTO,0603,15n,order confirmed; manufacturer drawing crosscheck pending
C15,CS2G_I3,GRM1885C1H222JA01D,0603,2.2n,topology corrected; physical CAD and supplier verification pending
R21,RPD_I3,RC0603FR-0710KL,0603,10k,topology corrected; physical CAD and supplier verification pending
R22,RFB_M1,RV0805FR-0722ML,0805,22Meg,10% exact order candidate; manufacturer evidence audit in progress
C16,CFB_M1,GRM1885C1H471JA01D,0603,470p,topology corrected; physical CAD and supplier verification pending
R23,RIN_M1,RC0603FR-07100KL,0603,100k,topology corrected; physical CAD and supplier verification pending
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
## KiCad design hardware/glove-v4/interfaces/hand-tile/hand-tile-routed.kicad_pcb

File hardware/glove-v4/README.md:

# Artisan right-hand capture glove — V4

Open the [local design viewer](../../docs/setup.md#design-viewer) to inspect the cuff, or follow the [assembly guide](guide/assembly.html). This public package preserves the engineering source and dated checks; [current status](../../docs/status.md) identifies the remaining physical and manufacturing work.

This is the current complete-camera design. The V3 tactile circuits and glove laminate are retained inside V4; V3 manufacturing files describe the earlier camera-free board.

The factory assembles and programs the cuff electronics, camera, battery, card and keyed harnesses. The wearer fits twenty prepared pressure/PVDF locations to the glove and plugs in the labeled branches. A local phone/laptop viewer shows contact, vibration, camera frames and acquisition status; the card retains full recordings.

| Function | Current implementation |
|---|---|
| Contact | 20 independent Velostat/Linqstat locations, 50 samples/s each; electrical levels until force calibration |
| Texture signal | 20 independent PVDF locations, 4,000 samples/s each; raw waveform, RMS/peak and spectrum |
| Cuff/camera motion | ISM330DHCXTR on the main PCB, 833 Hz |
| Hand motion | Separate 16×16 mm ISM330DHCXTR tile on the back of the hand, 833 Hz; keyed four-wire cable |
| Camera | CamThink 73.002.000035, OV5640, 120° diagonal field, 8 cm preset focus; VGA JPEG around 10 fps |
| Controller | ESP32-S3-WROOM-1-N8R8; USB-C; one button; RGB indicator |
| Communications | BLE setup/status/selected preview; Wi-Fi camera/full data and browser viewer; USB data |
| Recording | Kingston SDCIT2/32GB; timestamped checksummed streams and take labels |
| Battery | Protected Jauch 250480, 6.5 Ah minimum, 3.6 V; separate pack thermistor |

Two IMUs distinguish cuff/camera motion from the hand moving at the wrist. Joint angles and absolute hidden-hand position require their own tracking estimates and calibration. The current viewer uses a reference hand mesh; its colored sensing locations represent incoming contact measurements.

The six-hour continuous target has a 6.019-hour conservative energy scenario. The physical unit must pass the documented six-hour recording, temperature, card-capacity and rail tests. Radio throughput, force calibration and texture recognition depend on measured hardware/data evidence.

## Hardware verification —23 October

The [hardware evidence matrix](verification/hardware-coverage-matrix.md) inventories all561 fitted components and separates source/geometry checks, circuit models, firmware tests and physical qualification. The expanded [differential ADC simulation](verification/differential-adc/README.md) found a pressure-settling error; the actual firmware now waits24 µs for pressure and6 µs for acoustic samples. Five native cases pass the modeled settling criterion, and the corrected target image has been compiled and checked.

The [thermal screen](verification/thermal-screen/README.md) identifies heat-path and battery-mode temperature-readout work. [Combined20-channel analog runs](verification/coupled-analog/README.md) now retain one complete conditioned diagnostic with unresolved numerical sensitivity; [finite battery-path converter runs](power/battery-path-transient-review.md) still have numerical completion failures. These retain their native evidence and cannot count as full-system validation. Routing and final assembly release remain open.

## Files to use

- [System contract](system-contract.json): selections and remaining release work.
- [Visual assembly guide](guide/assembly.html) and [sensor/harness guide](guide/README.md).
- [Factory flashing and acceptance](guide/factory-flash-and-acceptance.md), [fillable acceptance record](guide/factory-record-template.json).
- [Main electrical source](electrical/components.json), [native schematic](electrical/glove-v4.kicad_sch), [pin/net reconciliation](electrical/native-net-reconciliation.json).
- [Dorsal hand tile](interfaces/hand-tile/): separate routed PCB and fabrication files.
- [Interactive cuff CAD](enclosure/viewer.html) and [enclosure specifications](enclosure/README.md): generated geometry, component-placement source and clearance evidence.
- [Two-IMU placement drawing](guide/dual-imu.svg): hand tile, cuff sensor and keyed cable.
- [Component/BOM source plan](procurement/bom-source-plan.csv), [main-board BOM](procurement/micron-v4-board-bom.csv) and [public sourcing scope](../../docs/source-inventory.md).
- [Power simulations](power/simulation/buck-results.json), [energy calculation](verification/energy-budget.md), [storage calculation](guide/storage-budget.json).
- [Firmware artifacts](../../firmware/tactile_v4/artifacts/) and [reproducible verification](../../docs/verification.md).

Main-board routing is active release work. The enclosure reports bind their clearance result to a particular component-placement hash; the current hardware matrix checks that correspondence. The published mechanical snapshot passed nominal CAD/STL checks; the rigid case is 112×104×45.5 mm, or 112×105.6×47.1 mm including the sheet window and flat carrier, with an estimated cuff mass of 218.2–233.2 g before external textile/harness. The preferred 50.8×38.1 mm footprint requires a different electronics/battery layout; [size audit](enclosure/compact-size-options.md) records the actual limits. [JLC3DP fabrication plan](procurement/jlc3dp-enclosure.md) separates printed shells from precision, optical and elastomer parts; process acceptance remains open. The exact assembled landed price is pending; the original $150–200 total is not established. Historical price observations and partial subtotals are identified as such. Supplier qualification and physical purchasing are separate project steps.

The2026-10-23 [shutdown review](verification/shutdown/README.md) corrected lost-supply handling, camera queue deadlines and premature rail shutdown. The local ESP32-S3 target build,34core+13HTTP sanitizer cases and9camera-driver cases pass. The phase fault matrix verifies owner acknowledgements and retry ordering; permanent driver/bus failures still require the independent hardware-reset design. The [temperature-readout/heat-path proposal](verification/thermal-screen/readout-proposal/README.md) has completed local model runs and clearance checks, with its remaining error/thermal bounds recorded explicitly. Those circuit and mechanical changes are still unapplied.

The [USB power-escape review](verification/power-escape-review/README.md) records the reviewed 20-open USB correction, applied to the canonical board in `097093661f7aa7e29208f5f636a8289161d4f53e`. It widens U32 OUT to 0.6 mm and connects U42 VBUS through a short fanout and a verified extension of POWER_A. Its calculated USB positive-copper resistance falls from 51.484 to 35.640 mΩ under the recorded assumptions; all 561 components and their pin mappings are preserved. Full thermal and remaining routing closure remain open. The [earlier review](verification/routing-proposal20/ARCHIVE-STATUS.md) retains the predecessor archive and findings. The current canonical board has 20 unconnected items, zero physical DRC errors and 561 components. The saved candidate archive and earlier 24-open descriptions are historical evidence; [current status](../../docs/status.md) binds these facts to the actual native board hash.

The [same-capability cost reduction](value-engineering/README.md) targets one-third of complete one-glove delivered cash cost. The first sourcing/model screen retains the full requirement lock, rejects shorter-runtime and failed-settling alternatives, and leaves both complete quote totals and qualification gates open.

The latest [temperature-policy implementation](verification/thermal-screen/readout-proposal/firmware/README.md) passes254 deterministic assertions and100,000 seeded ADC input checks under ASan/UBSan. It remains isolated from the target until the two-NTC circuit and load-control integration are applied. [Converter backend diagnostics](power/finite-path-backend-diagnostics/README.md) retain the final bounded ngspice failures and vendor simulator requirement. Repository checks after this work:516 tests and4 subtests passed; `node --check static/app.js` and `git diff --check` passed. These checks leave the manufacturing, numerical convergence and physical acceptance gates open.

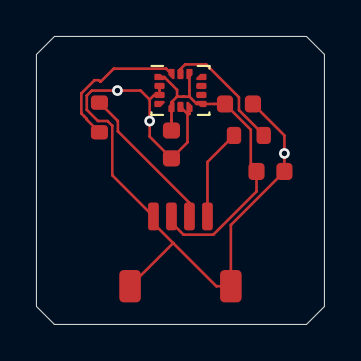
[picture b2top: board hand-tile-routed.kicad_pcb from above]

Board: 2 copper layers, 16.0 x 16.0 mm, 7 parts (0 on the bottom side), 6 nets.

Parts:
C1, C2: GRM188R71C104KA01D; C_0603_1608Metric
C3: GRM188R61A475KE15D; C_0603_1608Metric
J1: SM04B-SRSS-TB(LF)(SN); JST_SH_SM04B-SRSS-TB_1x04-1MP_P1.00mm_Horizontal
R1, R2: RC0603FR-0722RL; R_0603_1608Metric
U1: ISM330DHCXTR; ST_ISM330DHCX_LGA14_0.35mm

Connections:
3V3_SYS: C1.1, C2.1, C3.1, J1.2, U1.1, U1.5, U1.8, U1.12
GND: C1.2, C2.2, C3.2, J1.1, J1.MP, U1.2, U1.3, U1.6, U1.7
HAND_I2C_SCL: R2.2, U1.13
HAND_I2C_SDA: R1.2, U1.14
I2C_SCL: J1.4, R2.1
I2C_SDA: J1.3, R1.1
